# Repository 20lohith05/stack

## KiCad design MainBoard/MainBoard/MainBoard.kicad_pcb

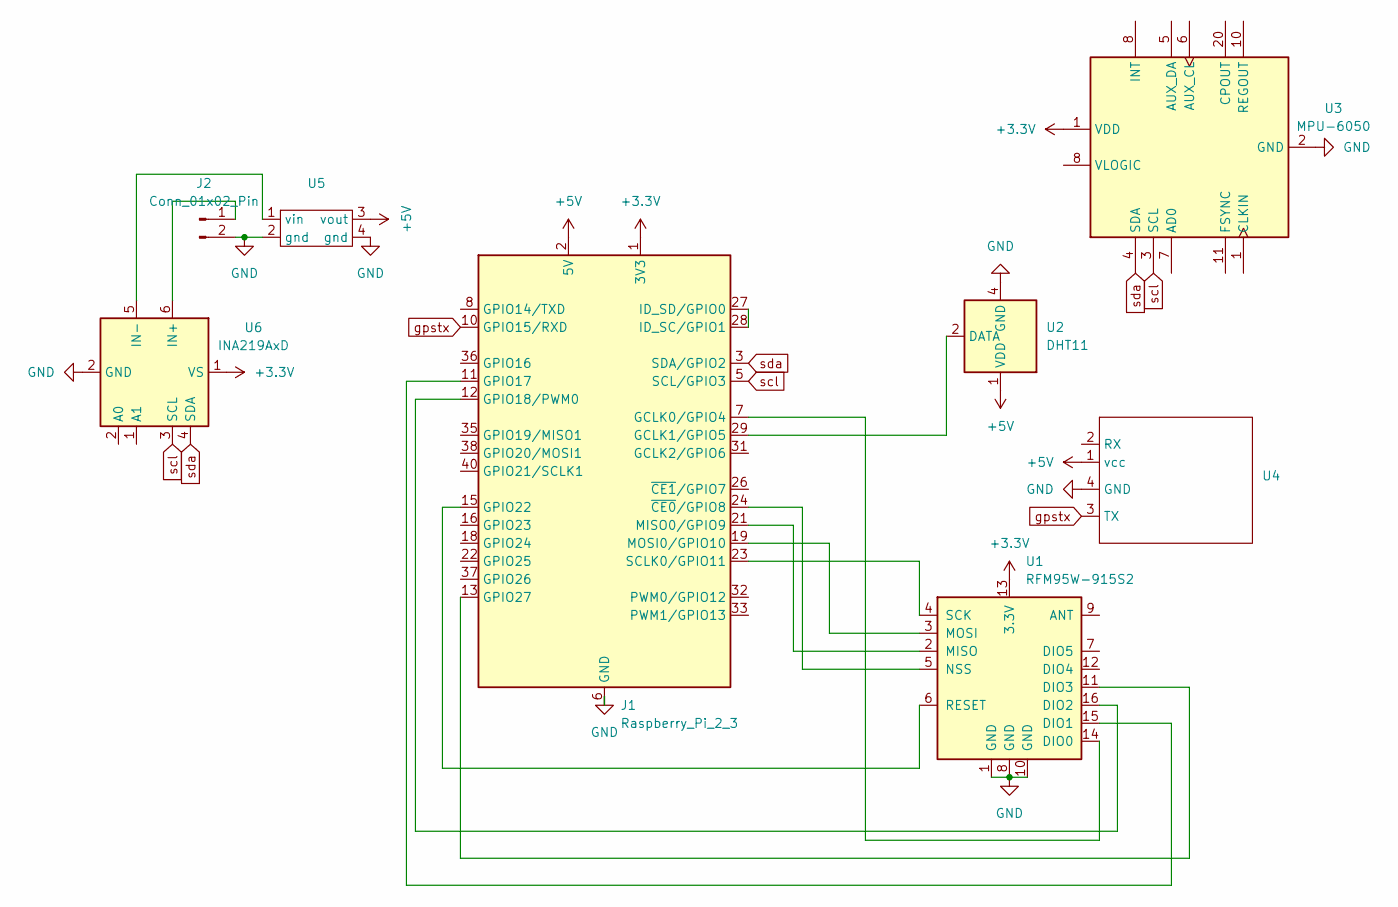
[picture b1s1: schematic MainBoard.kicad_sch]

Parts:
J1: Raspberry_Pi_2_3; PinSocket_2x20_P2.54mm_Vertical
J2: Conn_01x02_Pin; PinHeader_1x02_P2.54mm_Vertical
U1: RFM95W-915S2; HOPERF_RFM9XW_THT
U2: DHT11; Aosong_DHT11_5.5x12.0_P2.54mm
U3: MPU-6050; PinSocket_1x08_P2.54mm_Vertical
U4: PinSocket_1x04_P2.54mm_Vertical
U5: buck
U6: INA219AxD; PinSocket_1x06_P2.54mm_Vertical

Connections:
+3.3V: J1.1 (3V3), J1.17 (3V3), U1.13 (3.3V), U3.1 (VDD), U6.1 (VS)
+5V: J1.2 (5V), J1.4 (5V), U2.1 (VDD), U4.1 (vcc), U5.3 (vout)
GND: J1.6 (GND), J1.9 (GND), J1.14 (GND), J1.20 (GND), J1.25 (GND), J1.30 (GND), J1.34 (GND), J1.39 (GND), J2.2, U1.1 (GND), U1.8 (GND), U1.10 (GND), U2.4 (GND), U3.2 (GND), U4.4 (GND), U5.2 (gnd), U5.4 (gnd), U6.2 (GND)
unnamed: J1.7 (GCLK0/GPIO4), U1.14 (DIO0)
unnamed: J1.29 (GCLK1/GPIO5), U2.2 (DATA)
unnamed: J1.11 (GPIO17), U1.15 (DIO1)
unnamed: J1.12 (GPIO18/PWM0), U1.16 (DIO2)
unnamed: J1.15 (GPIO22), U1.6 (RESET)
unnamed: J1.13 (GPIO27), U1.11 (DIO3)
unnamed: J1.27 (ID_SD/GPIO0), J1.28 (ID_SC/GPIO1)
unnamed: J1.21 (MISO0/GPIO9), U1.2 (MISO)
unnamed: J1.19 (MOSI0/GPIO10), U1.3 (MOSI)
unnamed: J1.23 (SCLK0/GPIO11), U1.4 (SCK)
unnamed: J1.24 (~CE0/GPIO8), U1.5 (NSS)
unnamed: J2.1, U6.6 (IN+)
unnamed: U5.1 (vin), U6.5 (IN-)
gpstx: J1.10 (GPIO15/RXD), U4.3 (TX)
scl: J1.5 (SCL/GPIO3), U3.3 (SCL), U6.3 (SCL)
sda: J1.3 (SDA/GPIO2), U3.4 (SDA), U6.4 (SDA)

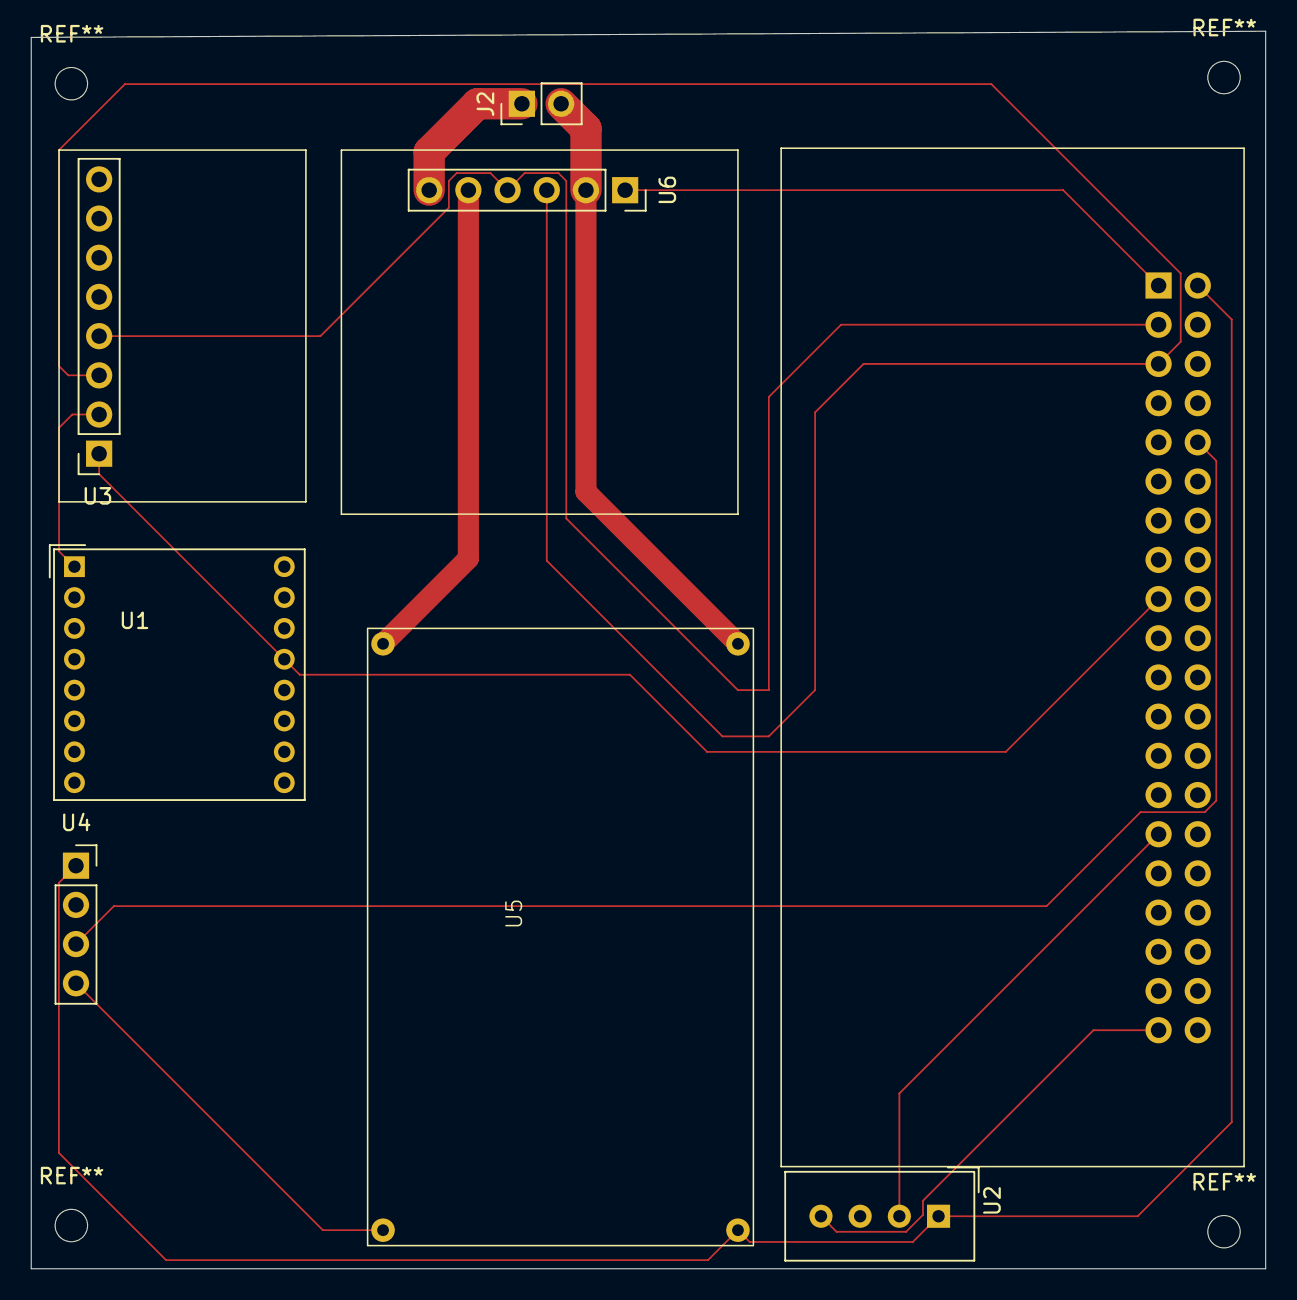
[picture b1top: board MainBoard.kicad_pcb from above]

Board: 2 copper layers, 80.0 x 80.2 mm, 8 parts (1 on the bottom side), 19 nets.
